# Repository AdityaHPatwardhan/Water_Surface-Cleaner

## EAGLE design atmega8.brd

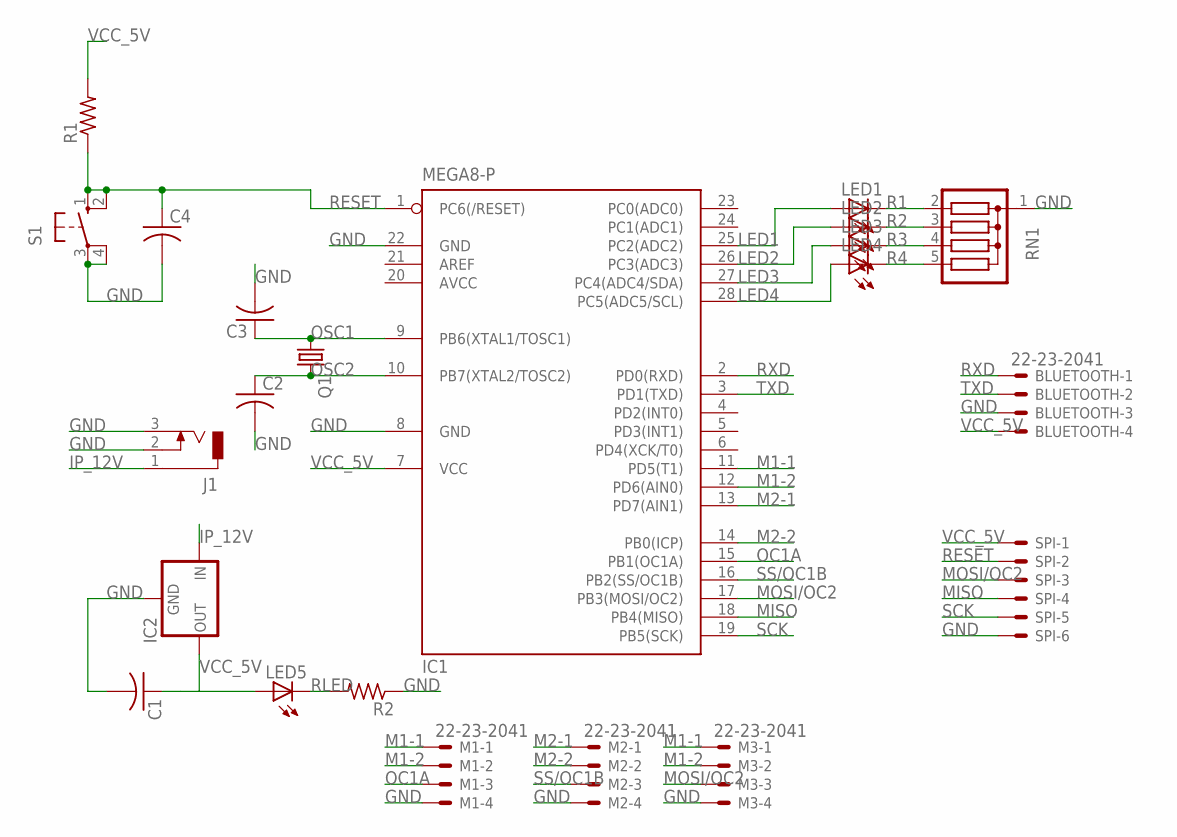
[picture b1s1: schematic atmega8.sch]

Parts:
BLUETOOTH: 22-23-2041
C1, C2, C3, C4: C-US050-025X075; C050-025X075
IC1: MEGA8-P; DIL28-3
IC2: 78XXL
J1: DCJ0303
LED1, LED2, LED3, LED4, LED5: LED3MM
M1, M2, M3: 22-23-2041
Q1: CRYSTALHC18U-V; HC18U-V
R1, R2: R-US_0204/7; 0204/7
RN1: G04R; SIL5
S1: 10-XX; B3F-10XX
SPI: 22-23-2061

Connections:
AVCC: IC1.20 (AVCC)
GND: BLUETOOTH.3, C1.2, C2.2, C3.2, C4.2, IC1.8 (GND), IC1.22 (GND), IC2.GND, J1.2, J1.3, M1.4, M2.4, M3.4, R2.1, RN1.1, S1.3, S1.4 (P1), SPI.6
IP_12V: IC2.IN, J1.1
LED1: IC1.25 (PC2(ADC2)), LED1.A
LED2: IC1.26 (PC3(ADC3)), LED2.A
LED3: IC1.27 (PC4(ADC4/SDA)), LED3.A
LED4: IC1.28 (PC5(ADC5/SCL)), LED4.A
M1-1: IC1.11 (PD5(T1)), M1.1, M3.1
M1-2: IC1.12 (PD6(AIN0)), M1.2, M3.2
M2-1: IC1.13 (PD7(AIN1)), M2.1
M2-2: IC1.14 (PB0(ICP)), M2.2
MISO: IC1.18 (PB4(MISO)), SPI.4
MOSI/OC2: IC1.17 (PB3(MOSI/OC2)), M3.3, SPI.3
OC1A: IC1.15 (PB1(OC1A)), M1.3
OSC1: C3.1, IC1.9 (PB6(XTAL1/TOSC1)), Q1.1
OSC2: C2.1, IC1.10 (PB7(XTAL2/TOSC2)), Q1.2
R1: LED1.K (C), RN1.2
R2: LED2.K (C), RN1.3
R3: LED3.K (C), RN1.4
R4: LED4.K (C), RN1.5
RESET: C4.1, IC1.1 (PC6(/RESET)), R1.1, S1.1 (S), S1.2 (S1), SPI.2
RLED: LED5.K (C), R2.2
RXD: BLUETOOTH.1, IC1.2 (PD0(RXD))
SCK: IC1.19 (PB5(SCK)), SPI.5
SS/OC1B: IC1.16 (PB2(SS/OC1B)), M2.3
TXD: BLUETOOTH.2, IC1.3 (PD1(TXD))
VCC_5V: BLUETOOTH.4, C1.1, IC1.7 (VCC), IC2.OUT, LED5.A, R1.2, SPI.1

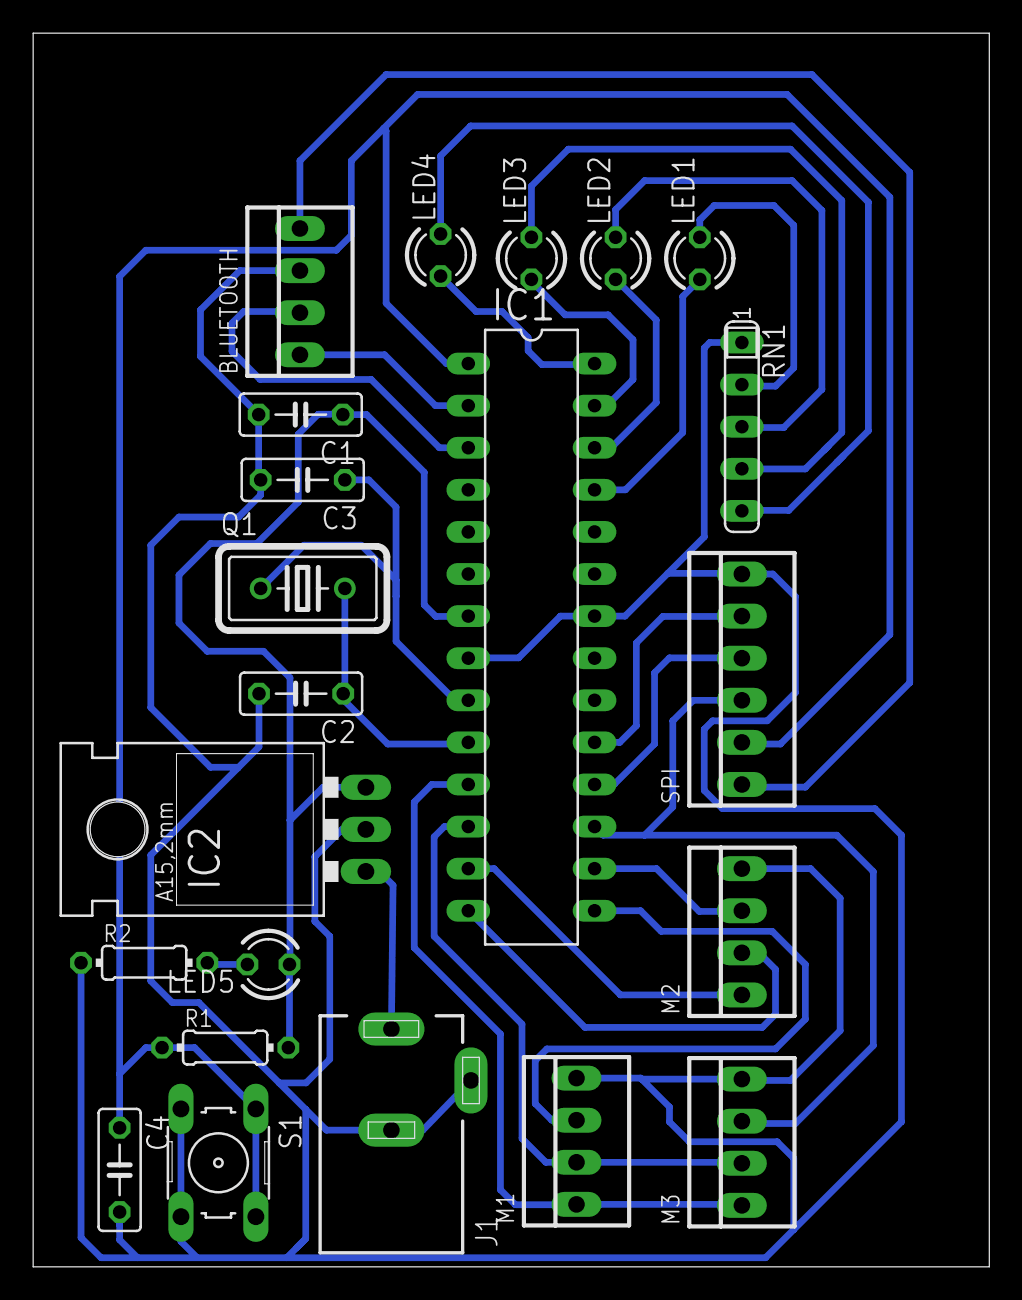
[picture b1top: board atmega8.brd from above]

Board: 2 copper layers, 57.7 x 74.5 mm, 22 parts (0 on the bottom side), 26 nets.
